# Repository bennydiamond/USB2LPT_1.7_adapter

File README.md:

USB2LPT rev 1.7 adapter board for Geeetech CY7C68013A development board

### Intro ###

This repository contains the schematic, PCB layout and pre-generated Gerber files. 
Since this adapter board contains no logic, no software is offered. For more information on USB2LPT device and to download necessary software files, please consult the [original creator's website](https://www-user.tu-chemnitz.de/~heha/basteln/PC/USB2LPT/).

USB2LPT is a "true" LPT (parallel) port to USB converter. It remaps the legacy LPT address to the USB board. This enables usage of a parallel port interface on modern computers when the communicating program uses fixed addressing (378H and 278H) to read and write to the parallel port. The process is complicated and make uses of dynamic re-addressing features present in Windows Environment debugging; which makes communication really slow.

This is currently the best and most compatible solution to interface legacy devices on parallel ports if your computer doesn't possess such interface.

### Usage ###

This adapter board transform the Geeetech CY7C68013A board into a USB2LPT rev 1.7 device.

**Please note that the LCSoft variant microcontroller board is not supported as the pinout is slightly different. 
The Geeetech variant has the RESET pushbutton near the USB connector whereas the LCSoft is located on the other side of the PCB.**

Geeetech variant:

LCSoft variant:

### Credits ###

USB2LPT original hardware design & software:
Henrik Haftmann

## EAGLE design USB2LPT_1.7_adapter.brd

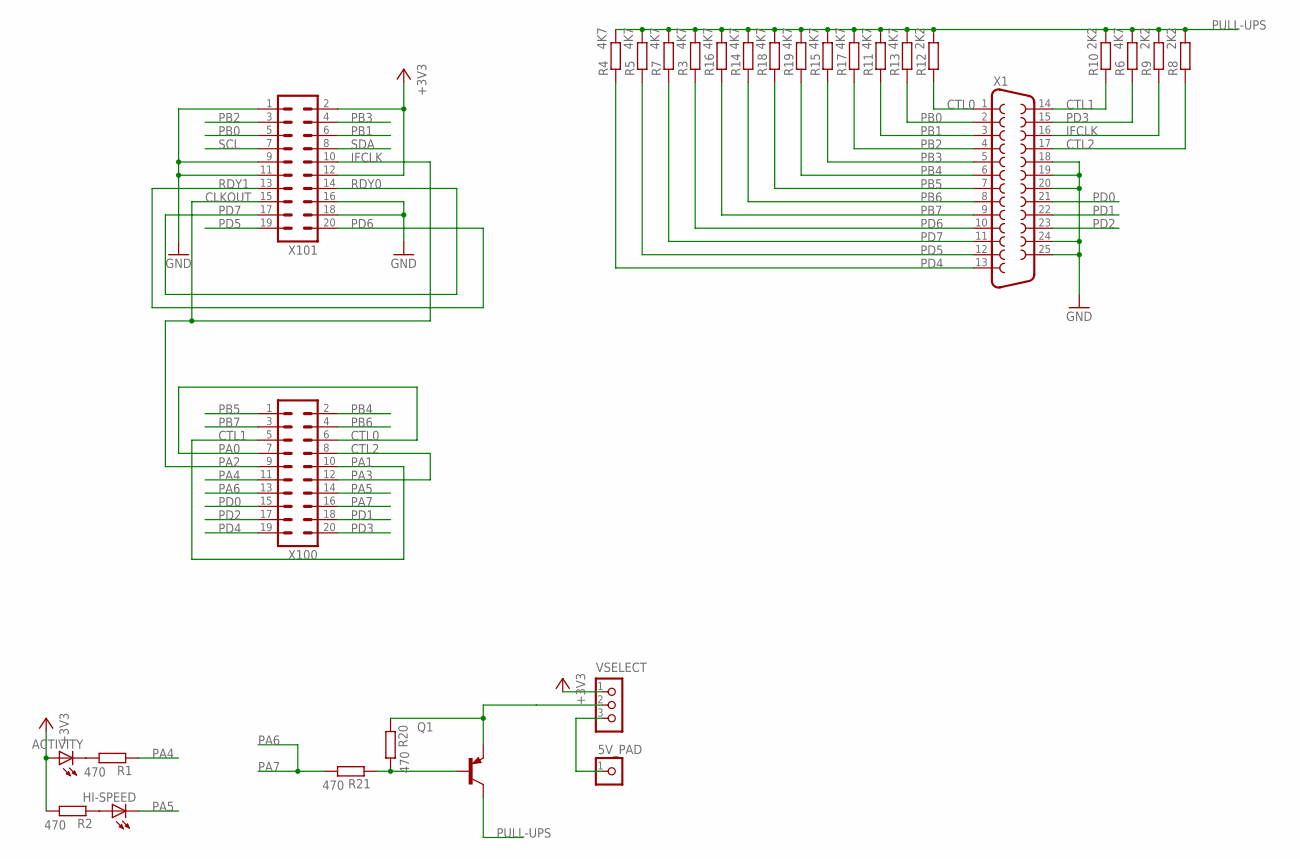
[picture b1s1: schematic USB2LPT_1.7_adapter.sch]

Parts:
+5V: CON_HEADER_1X01-PTH_08_17; M1X2_08_17
ACTIVITY: LED-0805; LED-805
HI-SPEED: LED-0805; LED-805
Q1: TRANSISTOR_BJT_PNP-SOT-23-BEC; SOT-23
R1, R2, R20, R21: 470; R805
R3, R4, R5, R6, R7, R11, R13, R14, R15, R16, R17, R18, R19: 4K7; R805
R8, R9, R10, R12: 2K2; R805
VSELECT: VSELECT_HEADER; HEADER_1X3
X1: F25D
X100, X101: MA10-2

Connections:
5V_PAD: +5V.1, VSELECT.3
+3V3: ACTIVITY.A, R2.2, VSELECT.1, X101.2, X101.12
CTL0: R12.1, X1.1, X100.6, X100.7
CTL1: R10.1, X1.14, X100.5, X100.10
CTL2: R8.1, X1.17, X100.8, X100.12
GND: X1.18, X1.19, X1.20, X1.24, X1.25, X101.1, X101.9, X101.11, X101.16, X101.18
IFCLK: R9.1, X1.16, X100.9, X101.10, X101.15
unnamed: HI-SPEED.A, R2.1
unnamed: ACTIVITY.C, R1.2
unnamed: Q1.1 (B), R20.2, R21.1
PA4: R1.1, X100.11
PA5: HI-SPEED.C, X100.14
PA6: R21.2, X100.13, X100.16
PB0: R13.1, X1.2, X101.5
PB1: R11.1, X1.3, X101.6
PB2: R17.1, X1.4, X101.3
PB3: R15.1, X1.5, X101.4
PB4: R19.1, X1.6, X100.2
PB5: R18.1, X1.7, X100.1
PB6: R14.1, X1.8, X100.4
PB7: R16.1, X1.9, X100.3
PD0: X1.21, X100.15
PD1: X1.22, X100.18
PD2: X1.23, X100.17
PD3: R6.1, X1.15, X100.20
PD4: R4.1, X1.13, X100.19
PD5: R5.1, X1.12, X101.19
PD6: R3.1, X1.10, X101.13, X101.20
PD7: R7.1, X1.11, X101.14, X101.17
PULL-UPS: Q1.3 (C), R3.2, R4.2, R5.2, R6.2, R7.2, R8.2, R9.2, R10.2, R11.2, R12.2, R13.2, R14.2, R15.2, R16.2, R17.2, R18.2, R19.2
SCL: X101.7
SDA: X101.8
VSELECT: Q1.2 (E), R20.1, VSELECT.2

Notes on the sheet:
PA0
PA1
PA3
CLKOUT
PA2
PA7
RDY0
RDY1

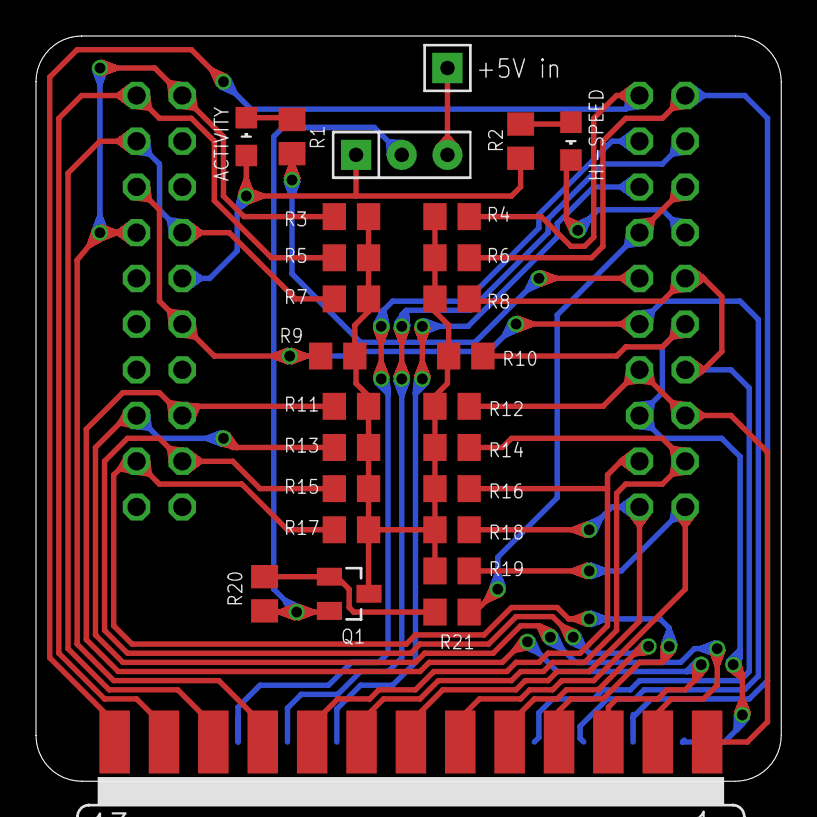
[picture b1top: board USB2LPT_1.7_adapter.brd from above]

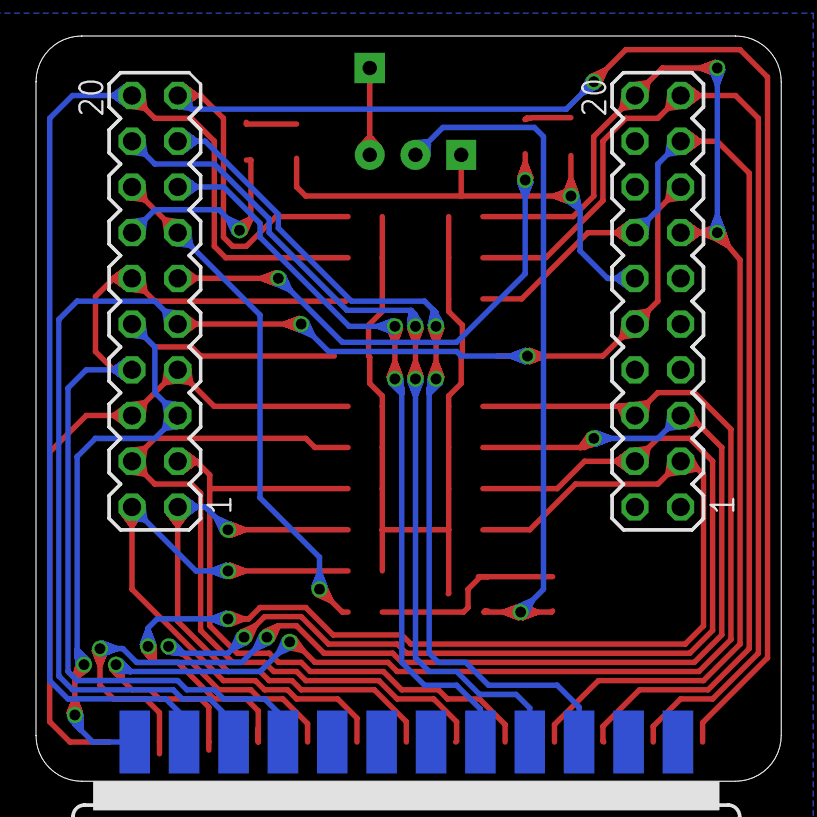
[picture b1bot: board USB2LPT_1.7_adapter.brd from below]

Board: 2 copper layers, 41.4 x 41.4 mm, 31 parts (2 on the bottom side), 31 nets.

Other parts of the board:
$$U$2: JUMP3_DESC_RIGHT
U$1: JUMP3_DESC_LEFT

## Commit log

2016-04-25 Initial commit PCB not done
2016-04-26 Board routing. Not quite done.
2016-04-26 Cleanup PCB some more
2016-04-27 idem
2016-05-02 Final revision of the board Added Gerber archive
2016-05-02 README.md edited online with Bitbucket

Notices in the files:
USB2LPT_1.7_adapter.brd:
Licensed under GPLv3
